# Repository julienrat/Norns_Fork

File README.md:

# Norns_Fork
**Dépôt Norns - installation Damien Skoraki**

L'idée principale est de forker l'officiel NORNS pour **la sublimer, la destructurer et la revisiter** avec un chapeau hifiberry DAC ADC Pro et des composants pas trop coûteux...

La doc du HIFIBERRY est ici : (https://www.hifiberry.com/docs/software/configuring-linux-3-18-x/)

## Modification du Kernel Original
Le noyau original  de norns ne contient pas les modules permettant le bon fonctionnement du chapeau HIFIBERRY, mais contient les modules de l'ecran !

D'autres noyaux sont présents dans la distribution officielle de Norns .... mais sans les modules de l'écran !

D'où le casse tête ! donc 2 solutions !

- Recompiler un noyau vierge sur une install vierge au risque de louper des trucs en s'inspirant du [vieux tuto](https://github.com/okyeron/norns-image/wiki/1.-Norns-2.0-Full-Build-on-RasPi)
- Partir du  dernier noyau de l'installation y ajouter l'écran en bénéficiant des modules installés d'office pour ce noyau et garder tous les fichiers de config de l'installation en s'inpirant de ce [tuto vieux aussi :D](https://github.com/okyeron/norns-image/wiki/Reference:--Compile-OLED-display-drivers)

J'ai décidé de choisir la seconde option ! on pars de l'existant, on modifie le vieux tuto ! et si ça bouge ce sera facile d'upgrader une image des familles !

**DONC :**

À partir de la realease NORNS **norns 220306**  :

[Images SD Norns](https://github.com/monome/norns-image/releases)

On flash une carte SD avec le logiciel Balena ETCHER : 

[Balena Etcher](https://www.balena.io/etcher/)

### On se connecte en ssh
```
ssh we@<adresse_ip>
Mot de passe : sleep
```
On étend la partition pour travailler à l'aise !
```
sudo raspi-config
```
et on reboot !

### Installation des paquets de compilation 
```
sudo apt-get update
sudo apt-get upgrade
sudo apt-get install flex bison raspberrypi-kernel-headers
sudo apt install build-essential fakeroot dpkg-dev perl libssl-dev bc gnupg dirmngr libncurses5-dev libelf-dev 
```
### On commente la derniere ligne du fichier /boot/config.txt

On édite

```
sudo nano /boot/config.txt
```
On va commenter cette ligne pour lancer la derniere version du kernel connue ! et non celle bidouillée par NORNS

```
#kernel=gnagnagna
```
et pendant qu'on est sur le fichier, on va commenter la ligne :
```
#dtoverlay=monome-snd-4271
```
et ajouter ces deux lignes pour utiliser la carte son du hifiberry adcplusdac-pro
```
dtoverlay=hifiberry-dacplusadcpro
force_eeprom_read=0
```
et on reboot ! et on jete un coup d'oeil sur la carte hifiberry, normalement les leds rouges doivent scintiller...

### Récupération du noyau pour compiler les modules:

```
git clone --depth=1 https://github.com/raspberrypi/linux
```

### On compile
on va récupérer les fichiers de config
```
cp /usr/src/linux-headers-$(uname -r)/Module.symvers .
cp /usr/src/linux-headers-$(uname -r)/.config .
```
ensuite on lance le menuconfig
```
make menuconfig
```
et on active l'écran !

```
Device Drivers  ---> Staging Drivers ---> Support for small TFT LCD display modules  --->
        <M>   SH1106 driver
        <M>   SSD1322 driver
```
et enfin on compile !
```
make -j4 prepare

make -j4 -C ~/linux SUBDIRS=drivers/staging/fbtft modules

```
on attends 3-4 heures ...

### Copie des modules et test
On va copier les modules compilés au bon endroit
```
sudo cp -v ~/linux/drivers/staging/fbtft/*.ko /lib/modules/$(uname -r)/kernel/drivers/staging/fbtft/

sudo depmod -a
```
et zou on teste !
```
sudo modprobe fbtft custom name=fb_ssd1322 debug=1 speed=16000000 gpios=reset:15,dc:14
dmesg
```

### On va tweaker !
L'écran est desormais monté sur /dev/fb1 au lieu de /dev/fb0, il va falloir modifier la configuration de **matron** interface graphique, pour rediriger l'affichage sur le bon point de montage :

On édite

```
nano ~/norns/matronrc.lua
```
et on change la ligne 2 pour pointer sur /dev/fb1

```
_boot.add_io('screen:fbdev', {dev='/dev/fb1'})
```
On reboot et voilà !

### TWEAKS !
Pour changer le nom du Norns, il suffit d'editer le fichier hostname situé dans /etc/ 
```
sudo nano /etc/hostname
```
Modifier le nom , puis sauver en appuyant sur Ctrl+X puis Y pour sauver

Il est aussi possible de modifier le nom directement sur la carte SD en ouvrant le repertoire /etc

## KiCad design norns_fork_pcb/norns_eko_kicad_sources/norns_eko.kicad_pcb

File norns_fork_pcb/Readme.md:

# Dossier PCB Norns Syst et Norns Eko

## Instructions de soudure :

* Soudure SYST : [https://rawcdn.githack.com/julienrat/Norns_Fork/main/norns_fork_pcb/norns_SYST_kicad_sources/ibom.html]

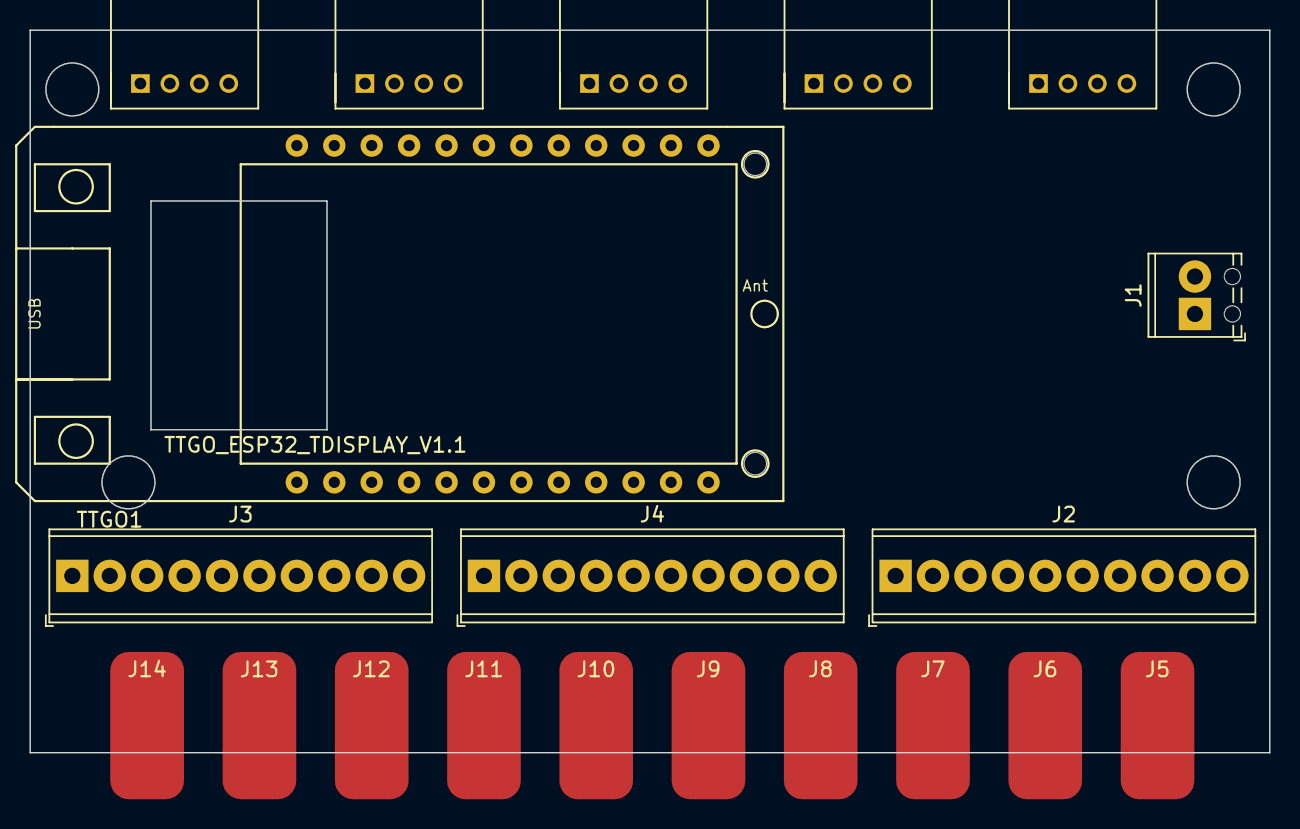
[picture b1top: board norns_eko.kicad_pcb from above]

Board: 2 copper layers, 84.1 x 49.0 mm, 20 parts (0 on the bottom side), 15 nets, no tracks yet.

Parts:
J1: Conn_01x02_Male; TerminalBlock_Phoenix_MPT-0,5-2-2.54_1x02_P2.54mm_Horizontal
J2: 3,3V; TerminalBlock_Phoenix_MPT-0,5-10-2.54_1x10_P2.54mm_Horizont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
J3: GND; TerminalBlock_Phoenix_MPT-0,5-10-2.54_1x10_P2.54mm_Horizont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
J4: Conn_01x10_Male; TerminalBlock_Phoenix_MPT-0,5-10-2.54_1x10_P2.54mm_Horizont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
J5, J6, J7, J8, J9, J10, J11, J12, J13, J14: Conn_01x01_Male; SolderWirePad_1x01_SMD_5x10mm
J15, J16, J17, J18, J19: GROVE-CONNECTOR-DIP-90D_4P-2.0_; HW4-2.0-90D
TTGO1: TTGO_ESP32_TDISPLAY_V1.1; TTGO_ESP32_TDisplay_v1.1

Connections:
+3V3: J2.1, J2.2, J2.3, J2.4, J2.5, J2.6, J2.7, J2.8, J2.9, J2.10, J15.2, J16.2, J17.2, J18.2, J19.2, TTGO1.12 (3.3V), TTGO1.24 (3.3V)
+5V: J1.2, TTGO1.1 (5V)
GND: J1.1, J3.1, J3.2, J3.3, J3.4, J3.5, J3.6, J3.7, J3.8, J3.9, J3.10, J15.1, J16.1, J17.1, J18.1, J19.1, TTGO1.2 (GND), TTGO1.13 (GND), TTGO1.14 (GND), TTGO1.22 (GND), TTGO1.23 (GND)
GPIO02 / TOUCH2/ ADC12: J4.10, J5.1, TTGO1.18 (GPIO2)
GPIO12 / TOUCH5 / ADC15: J4.7, J8.1, TTGO1.21 (GPIO12)
GPIO13 / TOUCH4 / ADC14: J4.8, J7.1, TTGO1.20 (GPIO13)
GPIO15 / TOUCH3 / ADC13: J4.9, J6.1, TTGO1.19 (GPIO15)
GPIO25 / DAC1 / ADC18: J4.3, J12.1, TTGO1.5 (GPIO25)
GPIO26 / DAC2 / ADC19: J4.2, J13.1, TTGO1.4 (GPIO26)
GPIO27 / TOUCH7 / ADC17: J4.6, J9.1, TTGO1.3 (GPIO27)
GPIO32 / TOUCH9 / ADC4: J4.4, J11.1, TTGO1.7 (GPIO32)
GPIO33 / TOUCH8/ ADC5: J4.5, J10.1, TTGO1.6 (GPIO33)
GPIO37: J4.1, J14.1
SCL: J15.4, J16.4, J17.4, J18.4, J19.4, TTGO1.16 (GPIO22)
SDA: J15.3, J16.3, J17.3, J18.3, J19.3, TTGO1.15 (GPIO21)

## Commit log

2022-05-17 Ajout des scripts TTGO T-display
2022-05-17 ajout du mapping de cablage
2022-05-18 Ajout du fichier Readme
2022-05-18 maj readme
2022-05-19 ajout du dossier images
2022-05-19 modif du boot pour residence temporaire
2022-06-02 ajout du PCB
2022-06-02 ajout de la BOM
2022-06-13 Create ToDoList
2022-06-13 Update ToDoList
2022-06-15 Create Boiboite
2022-06-15 mise a jour
2022-06-15 ajout EKO
2022-06-15 clean
2022-06-15 rename
2022-06-15 3D case for syst
2022-06-15 3D case for syst modif
2022-06-15 images
2022-06-15 Update PCB
2022-06-16 suppression repertoire en doublon
2022-06-17 mise a jour du PCB
2022-06-23 ajout 3D
2022-07-01 pcb_step v4
2022-07-01 ajout V3 du Norns
2022-07-06 mise a jour du dépot
2022-07-08 mise a jour du PCB avec les masques
2022-08-19 modif readme pour changement de nom norns
2022-08-19 timeout sur la connection wifi de 10 secondes
2022-08-19 gestion affichage boot
2022-08-26 debug osc
2022-08-26 newboot
